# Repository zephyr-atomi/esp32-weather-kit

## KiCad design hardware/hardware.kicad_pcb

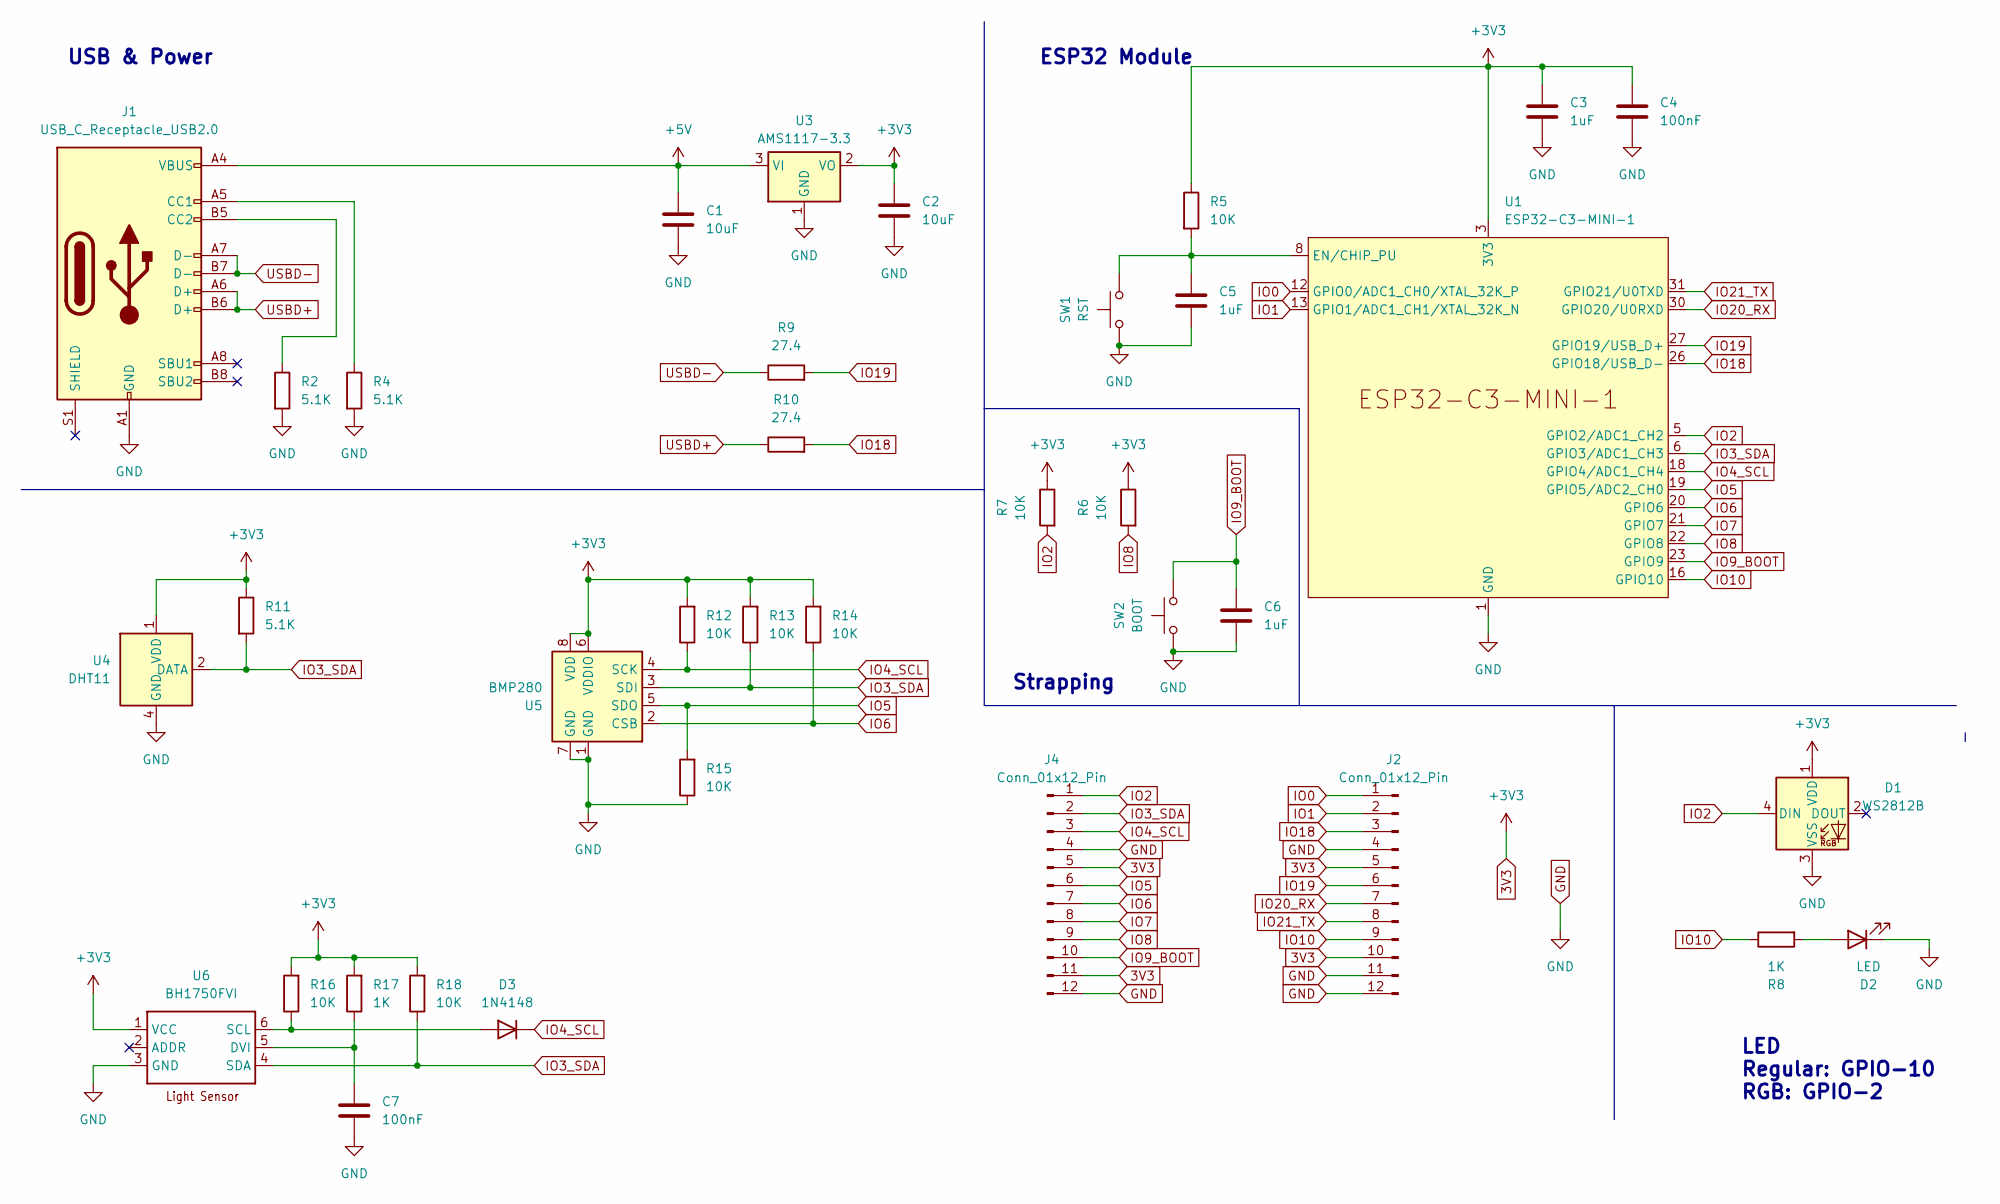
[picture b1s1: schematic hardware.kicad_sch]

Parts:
C1, C2: 10uF; C_0805_2012Metric
C3, C5, C6: 1uF; C_0402_1005Metric
C4, C7: 100nF; C_0402_1005Metric
D1: WS2812B; LED_WS2812B_PLCC4_5.0x5.0mm_P3.2mm
D2: LED; LED_0603_1608Metric
D3: 1N4148; D_DO-35_SOD27_P7.62mm_Horizontal
J1: USB_C_Receptacle_USB2.0; USB_C_Receptacle_HRO_TYPE-C-31-M-12
J2, J4: Conn_01x12_Pin; PinHeader_1x12_P2.54mm_Vertical
R2, R4, R11: 5.1K; R_0402_1005Metric
R5, R6, R7, R12, R13, R14, R15, R16, R18: 10K; R_0402_1005Metric
R8, R17: 1K; R_0402_1005Metric
R9, R10: 27.4; R_0402_1005Metric
SW1: RST; SW_SPST_PTS810
SW2: BOOT; SW_SPST_PTS810
U1: ESP32-C3-MINI-1
U3: AMS1117-3.3; SOT-223-3_TabPin2
U4: DHT11; Aosong_DHT11_5.5x12.0_P2.54mm
U5: BMP280; Bosch_LGA-8_2x2.5mm_P0.65mm_ClockwisePinNumbering
U6: BH1750FVI; 6-WSOF-BH1750

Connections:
3V3: C2.1, C3.1, C4.1, D1.1 (VDD), J2.5, J2.10, J4.5, J4.11, R5.1, R6.1, R7.1, R11.1, R12.2, R13.2, R14.2, R16.2, R17.2, R18.2, U1.3 (3V3), U3.2 (VO), U4.1 (VDD), U5.6 (VDDIO), U5.8 (VDD), U6.1 (VCC)
+5V: C1.1, J1.A4 (VBUS), J1.A9 (VBUS), J1.B4 (VBUS), J1.B9 (VBUS), U3.3 (VI)
GND: C1.2, C2.2, C3.2, C4.2, C5.2, C6.2, C7.2, D1.3 (VSS), D2.1 (K), J1.A1 (GND), J1.A12 (GND), J1.B1 (GND), J1.B12 (GND), J2.4, J2.11, J2.12, J4.4, J4.12, R2.2, R4.2, R15.1, SW1.1, SW2.2, U1.1 (GND), U1.2 (GND), U1.11 (GND), U1.14 (GND), U1.36 (GND), U1.37 (GND), U1.38 (GND), U1.39 (GND), U1.40 (GND), U1.41 (GND), U1.42 (GND), U1.43 (GND), U1.44 (GND), U1.45 (GND), U1.46 (GND), U1.47 (GND), U1.48 (GND), U1.49 (GND), U1.50 (GND), U1.51 (GND), U1.52 (GND), U1.53 (GND), U3.1 (GND), U4.4 (GND), U5.1 (GND), U5.7 (GND), U6.3 (GND)
IO0: J2.1, U1.12 (GPIO0/ADC1_CH0/XTAL_32K_P)
IO1: J2.2, U1.13 (GPIO1/ADC1_CH1/XTAL_32K_N)
IO2: D1.4 (DIN), J4.1, R7.2, U1.5 (GPIO2/ADC1_CH2)
IO3_SDA: J4.2, R11.2, R13.1, R18.1, U1.6 (GPIO3/ADC1_CH3), U4.2 (DATA), U5.3 (SDI), U6.4 (SDA)
IO4_SCL: D3.1 (K), J4.3, R12.1, U1.18 (GPIO4/ADC1_CH4), U5.4 (SCK)
IO5: J4.6, R15.2, U1.19 (GPIO5/ADC2_CH0), U5.5 (SDO)
IO6: J4.7, R14.1, U1.20 (GPIO6), U5.2 (CSB)
IO7: J4.8, U1.21 (GPIO7)
IO8: J4.9, R6.2, U1.22 (GPIO8)
IO9_BOOT: C6.1, J4.10, SW2.1, U1.23 (GPIO9)
IO10: J2.9, R8.1, U1.16 (GPIO10)
IO18: J2.3, R10.2, U1.26 (GPIO18/USB_D-)
IO19: J2.6, R9.2, U1.27 (GPIO19/USB_D+)
IO20_RX: J2.7, U1.30 (GPIO20/U0RXD)
IO21_TX: J2.8, U1.31 (GPIO21/U0TXD)
unnamed: D2.2 (A), R8.2
unnamed: D3.2 (A), R16.1, U6.6 (SCL)
unnamed: J1.A5 (CC1), R4.1
unnamed: J1.B5 (CC2), R2.1
unnamed: C5.1, R5.2, SW1.2, U1.8 (EN/CHIP_PU)
unnamed: C7.1, R17.1, U6.5 (DVI)
USBD+: J1.A6 (D+), J1.B6 (D+), R10.1
USBD-: J1.A7 (D-), J1.B7 (D-), R9.1

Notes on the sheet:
ESP32 Module
USB & Power
LED Regular: GPIO-10 RGB: GPIO-2
Strapping

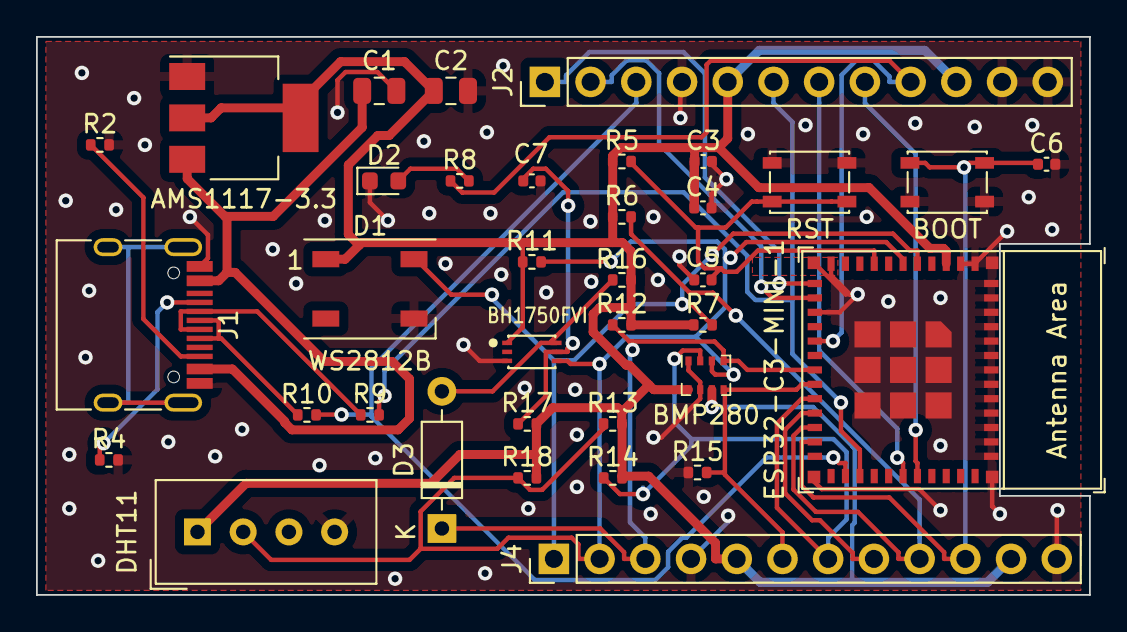
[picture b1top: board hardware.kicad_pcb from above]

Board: 2 copper layers, 58.5 x 31.0 mm, 36 parts (0 on the bottom side), 26 nets.

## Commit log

2023-12-22 First ver
2023-12-23 A work version for all devices: - DHT11 - BMP180 (I2C) - BH1750 (I2C) - SSD1306 (I2C, Display)
2023-12-26 hardware schematic ready.
2023-12-27 Auto routing for PCB by free-routing.
2023-12-27 PCB is ready for print.
2024-01-01 Draft version to enable stepper.
    And have some changes on KiCad data, may have something wrong. Let's just keep them now.
2024-01-01 Passed A4988.
2024-04-07 Failed on enabling CANbus on ESP32C3. A checkpoint for fix-up in the future.
2024-05-09 Enabled CAN on ESP32C3.
    Please don't use GPIO 1 for RX, due to issue here: https://github.com/esp-rs/esp-hal/issues/1207
